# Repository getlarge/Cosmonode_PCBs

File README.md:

# Cosmonode v0.7

Universal node, plug and play extensions to ease sensors connection.

### Features

	- Compile and flash with Arduino IDE
	- MCU = ATMega328P-AU
	- radio = RN2483 / RFM69CW ( communications based on LoRaWan or MySensors protocol )
	- 3.3V regulation ( XC6206P332MR )
	- Powered by 3.7V LiPo battery ( 2 pins JST connector )
	- Battery charging ( MCP7831 )
	- State LED's
	- Jumpers to activate radio reset, LED's, on/off switch
	- Button for reset / config mode, or anything else!
	- ATSHA204 to allow hardware unique signature ( no use with RN2483 )

### Projects

Each directory contains Kicad plans, 3D plans, gerber, descriptive .png and .pdf files.

	- ext01 : BME280, Temperature + Humidity + Pression sensor ( only here for the footprint )
	- ext02 : XKC-Y25, Liquid level sensor
	- ext03 : Various connectors ( I2C, Digital, Analog )
	- ext04 : PT100 3 wire, Temperature sensor
	- ext05 : ISP header + micro USB to TTL 
	- ext06 : Analog pH Sensor - BNC probe (WIP)
	- ext07 : MHZ19, CO2 sensor

### Board pinout

	- A0 = /
	- A1 = /
	A2 = ATSHA204 Input
	A3 = Battery voltage report
	A4 = SDA
	A5 = SCL
	A6 = * LED, jumper J9 ( used as RN2483 Tx )
	A7 = * LED, jumper J14 ( used as RN2483 Rx )
	D0 = RX
	D1 = TX
	D2 = * WakeInterrupt from RN2483, jumper J6 - RFM69 DI0
	D3 = ButtonInterrupt, jumper JP2 ( used to chose mode )
	D4 = /
	D5 = /
	D6 = /
	D7 = /
	D8 = /
	D9 = * RN2483 Reset, jumper J3 - RFM69 Reset
	D10 = RN2483 Rx - RFM69 NSS
	D11 = RN2483 Tx - RFM69 MOSI
	D12 = RFM69 MISO
	D13 = RFM69 SCK
	*optionnal, solder jumper

### Roadmap

--> changelog.md

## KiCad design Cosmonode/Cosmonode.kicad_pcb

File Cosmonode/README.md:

# Cosmonode

The core is based on ATMega328P-AU, RFM69CW, M25P40

Features :

- Compile and flash with arduino
- RF communications based on MySensors protocol
- OTA upload
- Powered by LiPo battery ( 2 pins JST connector )
- ATSHA204 to allow hardware unique signature 
- Universal node, plug and play extensions to ease sensors connection

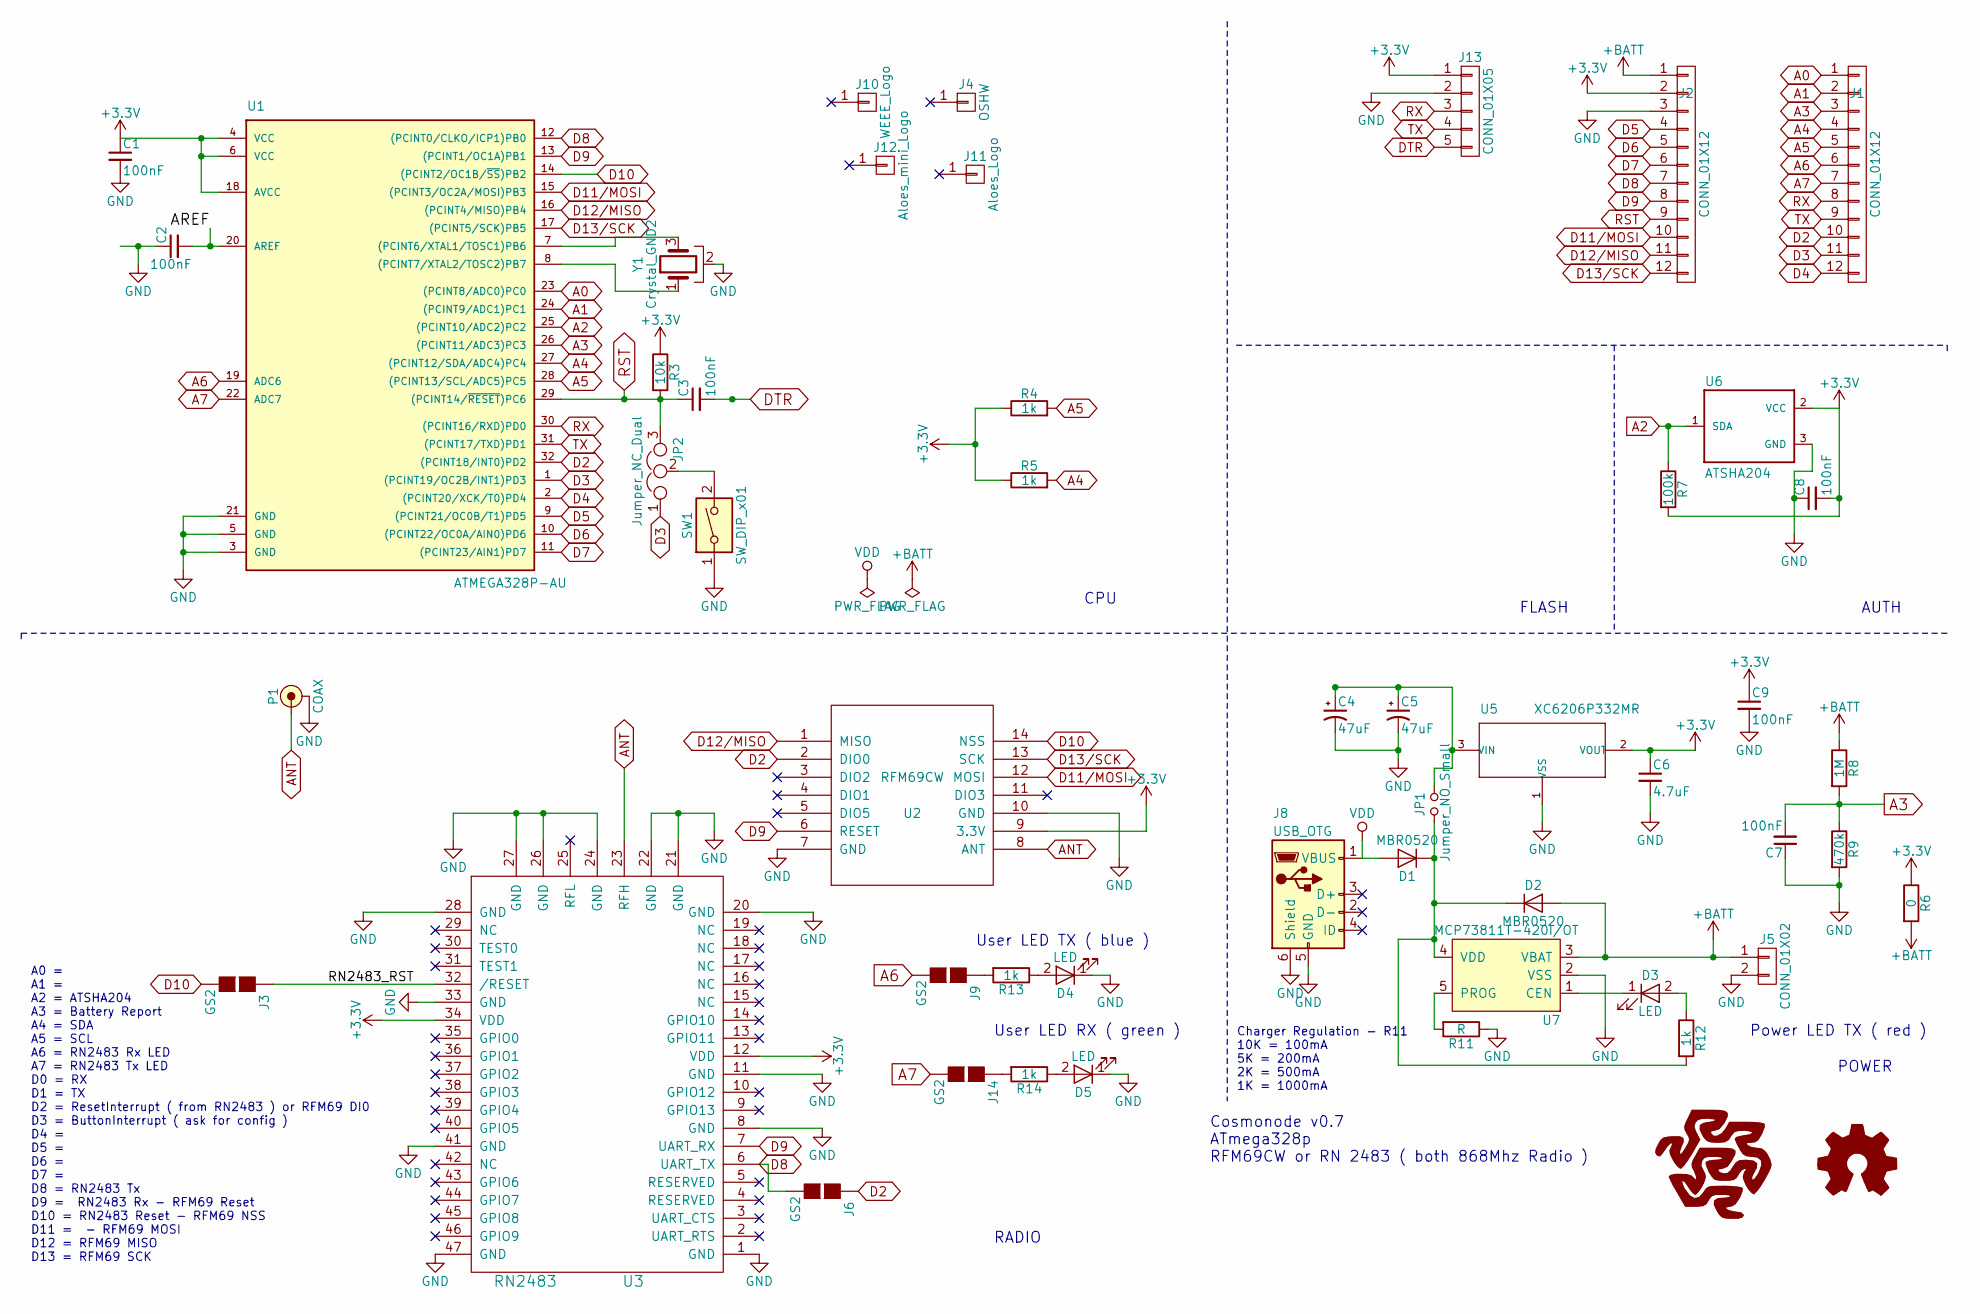
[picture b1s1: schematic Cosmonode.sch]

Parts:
C1, C2, C3, C7, C8, C9: 100nF; C_0603_HandSoldering
C4, C5: 47uF; CP_Tantalum_Case-A_EIA-3216-18_Reflow
C6: 4.7uF; C_0603_HandSoldering
D1, D2: MBR0520; D_SOD-123
D3, D4, D5: LED; LED_0603_HandSoldering
J1, J2: CONN_01X12; Pin_Header_Straight_1x12_Pitch2.54mm
J3, J6, J9, J14: GS2
J4: OSHW; OSHW-Logo_7.5x8mm_Copper
J5: CONN_01X02; JST_PH_B2B-PH-K_02x2.00mm_Straight
J8: USB_OTG; USB_Micro-B_Molex-105017-0001
J10: WEEE_Logo; WEEE-Logo_4.2x6mm_SilkScreen
J11: Aloes_Logo; Aloes
J12: Aloes_mini_Logo; Aloes_mini
J13: CONN_01X05; Pin_Header_Straight_1x05_Pitch2.54mm
JP1: Jumper_NO_Small; Pin_Header_Straight_1x02_Pitch2.54mm
JP2: Jumper_NC_Dual; Pin_Header_Straight_1x03_Pitch2.54mm
P1: COAX; EDGE_SMA_5; Farnell 1608592
R3: 10k; R_0603_HandSoldering
R4, R5, R12, R13, R14: 1k; R_0603_HandSoldering
R6: 0; R_0603_HandSoldering
R7: 100k; R_0603_HandSoldering
R8: 1M; R_0603_HandSoldering
R9: 470k; R_0603_HandSoldering
R11: R; R_0603_HandSoldering
SW1: SW_DIP_x01; SW_Tactile_SPST_Angled_PTS645Vx58-2LFS
U1: ATMEGA328P-AU; TQFP-32_7x7mm_Pitch0.8mm
U2: RFM69CW; RFM12B_SMD
U3: RN2483
U5: XC6206P332MR; TSOT-23
U6: ATSHA204; TSOT-23
U7: MCP73811T-420I/OT; SOT-23-5_HandSoldering
Y1: Crystal_GND2; X3-SMD-3.6X1.3X0.8MM

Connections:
+3V3: C1.1, C6.1, C8.2, C9.1, J2.2, J13.1, R3.1, R4.1, R5.1, R6.1, R7.2, U1.4 (VCC), U1.6 (VCC), U1.18 (AVCC), U2.9 (3.3V), U3.12 (VDD), U3.34 (VDD), U5.2 (VOUT), U6.2 (VCC)
+BATT: D2.2 (A), J2.1, J5.1, R6.2, R8.1, U7.3 (VBAT)
/AREF: C2.2, U1.20 (AREF)
/RN2483_RST: J3.1 (G1), U3.32 (/RESET)
A0: J1.1, U1.23 ((PCINT8/ADC0)PC0)
A1: J1.2, U1.24 ((PCINT9/ADC1)PC1)
A2: R7.1, U1.25 ((PCINT10/ADC2)PC2), U6.1 (SDA)
A3: C7.2, J1.3, R8.2, R9.1, U1.26 ((PCINT11/ADC3)PC3)
A4: J1.4, R5.2, U1.27 ((PCINT12/SDA/ADC4)PC4)
A5: J1.5, R4.2, U1.28 ((PCINT13/SCL/ADC5)PC5)
A6: J1.6, J9.2 (G2), U1.19 (ADC6)
A7: J1.7, J14.2 (G2), U1.22 (ADC7)
ANT: P1.1 (RF), U2.8 (ANT), U3.23 (RFH)
D2: J1.10, J6.1 (G1), U1.32 ((PCINT18/INT0)PD2), U2.2 (DIO0)
D3: J1.11, JP2.1, U1.1 ((PCINT19/OC2B/INT1)PD3)
D4: J1.12, U1.2 ((PCINT20/XCK/T0)PD4)
D5: J2.4, U1.9 ((PCINT21/OC0B/T1)PD5)
D6: J2.5, U1.10 ((PCINT22/OC0A/AIN0)PD6)
D7: J2.6, U1.11 ((PCINT23/AIN1)PD7)
D8: J2.7, J6.2 (G2), U1.12 ((PCINT0/CLKO/ICP1)PB0), U3.6 (UART_TX)
D9: J2.8, U1.13 ((PCINT1/OC1A)PB1), U2.6 (RESET), U3.7 (UART_RX)
D10: J3.2 (G2), U1.14 ((PCINT2/OC1B/~SS~)PB2), U2.14 (NSS)
D11/MOSI: J2.10, U1.15 ((PCINT3/OC2A/MOSI)PB3), U2.12 (MOSI)
D12/MISO: J2.11, U1.16 ((PCINT4/MISO)PB4), U2.1 (MISO)
D13/SCK: J2.12, U1.17 ((PCINT5/SCK)PB5), U2.13 (SCK)
DTR: C3.2, J13.5
GND: C1.2, C2.1, C4.2, C5.2, C6.2, C7.1, C8.1, C9.2, D4.1 (K), D5.1 (K), J2.3, J5.2, J8.5 (GND), J8.6 (Shield), J13.2, P1.2 (GND), R9.2, R11.1, SW1.1, U1.3 (GND), U1.5 (GND), U1.21 (GND), U2.7 (GND), U2.10 (GND), U3.1 (GND), U3.8 (GND), U3.11 (GND), U3.20 (GND), U3.21 (GND), U3.22 (GND), U3.24 (GND), U3.26 (GND), U3.27 (GND), U3.28 (GND), U3.33 (GND), U3.41 (GND), U3.47 (GND), U5.1 (VSS), U6.3 (GND), U7.2 (VSS), Y1.2
unnamed: C4.1, C5.1, JP1.2, U5.3 (VIN)
unnamed: D1.1 (K), D2.1 (K), JP1.1, R12.2, U7.4 (VDD)
unnamed: D3.1 (K), U7.1 (CEN)
unnamed: D3.2 (A), R12.1
unnamed: D4.2 (A), R13.1
unnamed: D5.2 (A), R14.1
unnamed: J9.1 (G1), R13.2
unnamed: J14.1 (G1), R14.2
unnamed: JP2.2, SW1.2
unnamed: R11.2, U7.5 (PROG)
unnamed: U1.7 ((PCINT6/XTAL1/TOSC1)PB6), Y1.3
unnamed: U1.8 ((PCINT7/XTAL2/TOSC2)PB7), Y1.1
RST: C3.1, J2.9, JP2.3, R3.2, U1.29 ((PCINT14/~RESET~)PC6)
RX: J1.8, J13.3, U1.30 ((PCINT16/RXD)PD0)
TX: J1.9, J13.4, U1.31 ((PCINT17/TXD)PD1)
VDD: D1.2 (A), J8.1 (VBUS)

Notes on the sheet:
CPU
FLASH
AUTH
POWER
RADIO
Cosmonode v0.7 ATmega328p RFM69CW or RN 2483 ( both 868Mhz Radio )
Charger Regulation - R11 10K = 100mA 5K = 200mA 2K = 500mA 1K = 1000mA
User LED TX ( blue )
User LED RX ( green )
Power LED TX ( red )
A0 = A1 = A2 = ATSHA204 A3 = Battery Report A4 = SDA A5 = SCL A6 = RN2483 Rx LED A7 = RN2483 Tx LED D0 = RX D1 = TX D2 = ResetInterrupt ( from RN2483 ) or RFM69 DI0 D3 = ButtonInterrupt ( ask for config ) D4 = D5 = D6 = D7 = D8 = RN2483 Tx D9 = RN2483 Rx - RFM69 Reset D10 = RN2483 Reset - RFM69 NSS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

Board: 2 copper layers, 49 parts (6 on the bottom side), 43 nets, no tracks yet.

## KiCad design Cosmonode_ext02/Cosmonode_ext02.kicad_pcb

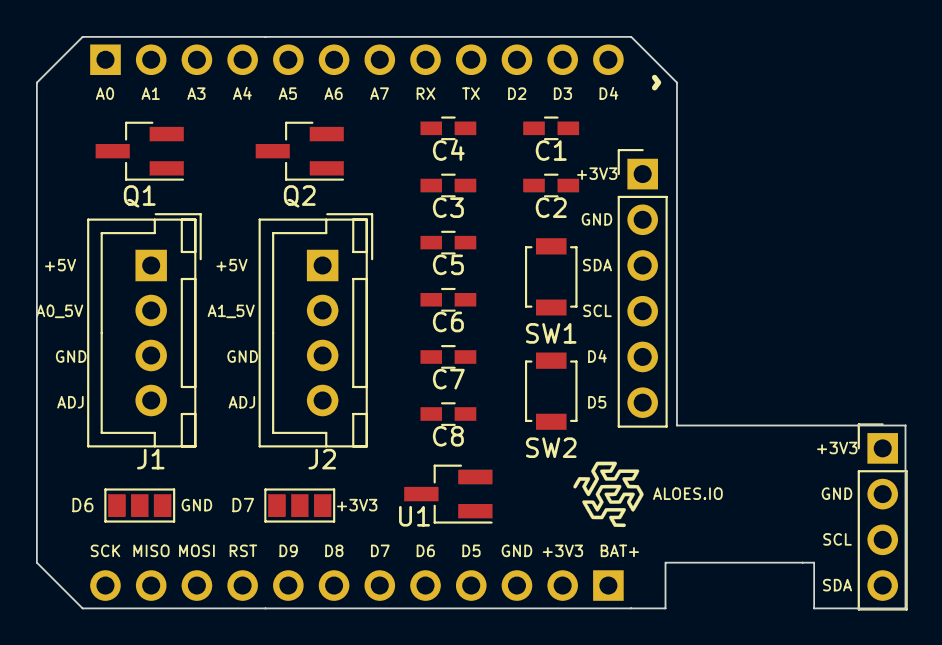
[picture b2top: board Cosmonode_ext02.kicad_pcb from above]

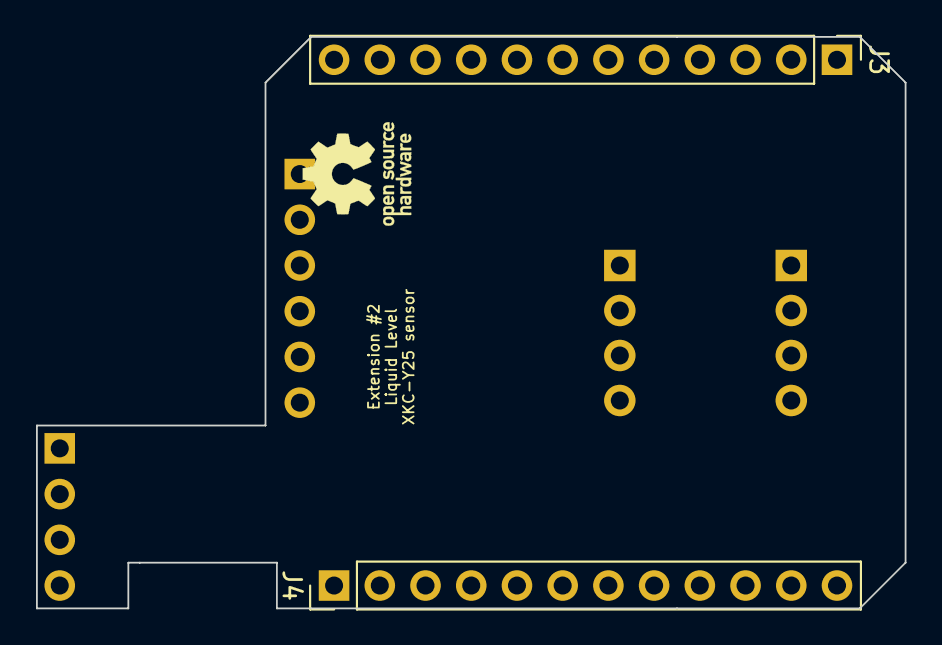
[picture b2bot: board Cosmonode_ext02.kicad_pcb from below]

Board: 2 copper layers, 48.3 x 31.8 mm, 23 parts (3 on the bottom side), 17 nets, no tracks yet.

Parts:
C1, C3, C4, C5, C7, C8: 100nF; C_0603_HandSoldering
C2, C6: 10uF; C_0603_HandSoldering
J1, J2: CONN_01X04; JST_XH_B04B-XH-A_04x2.50mm_Straight
J3, J4: CONN_01X12; Socket_Strip_Straight_1x12_Pitch2.54mm
J5, J6: GS3
J7: Aloes_Logo; Aloes_mini
J8: OSHW_Logo; OSHW-Logo_5.7x6mm_SilkScreen
J9: CONN_01X04; Socket_Strip_Straight_1x04_Pitch2.54mm
J10: CONN_01X06; Pin_Header_Straight_1x06_Pitch2.54mm
Q1, Q2: BSS138; SOT-23_Handsoldering
SW1, SW2: SW_Push; SW_SPST_B3U-1000P
U1: XC6206P502MR; SOT-23_Handsoldering

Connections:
+3V3: J4.2, J5.3, J9.1, J10.1, Q1.1, Q2.1
+5V: C2.1, C3.1, C6.1, C7.1, J1.1, J2.1, U1.2
A0: J3.1, Q1.2
A0_5V: C4.1, J1.2, Q1.3
A1: J3.2, Q2.2
A1_5V: C8.1, J2.2, Q2.3
A4: J3.4, J9.4, J10.3
A5: J3.5, J9.3, J10.4
D4: J3.12, J10.5
D5: J4.4, J10.6
D6: J4.5, J6.1
D7: J4.6, J5.1
GND: J4.3, J6.3, J9.2, J10.2
unnamed: C1.1, C2.2, C3.2, C4.2, C5.1, C6.2, C7.2, C8.2, J1.3, J2.3, J6.2, SW1.2, SW2.2, U1.1
unnamed: C1.2, J1.4, SW1.1
unnamed: C5.2, J2.4, SW2.1
unnamed: J5.2, U1.3

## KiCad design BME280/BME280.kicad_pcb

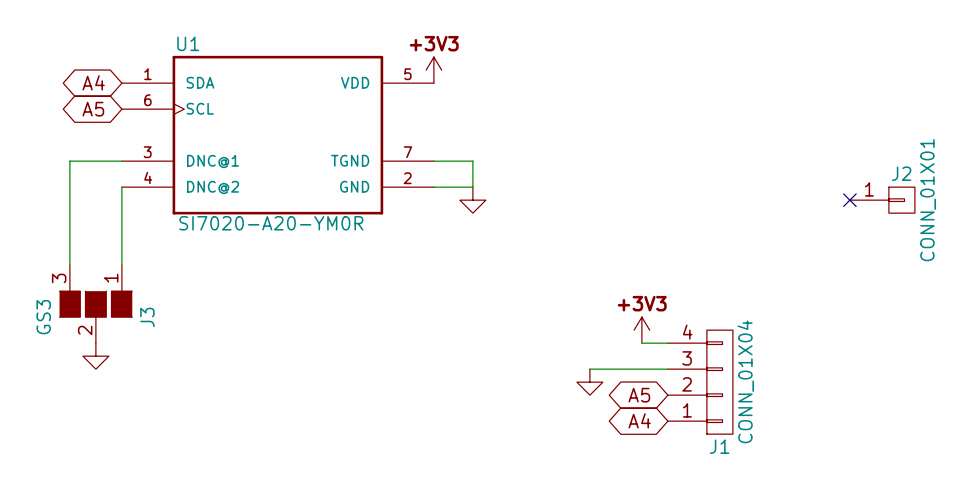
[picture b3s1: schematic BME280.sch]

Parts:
J1: CONN_01X04; Pin_Header_Angled_1x04_Pitch2.54mm
J2: CONN_01X01; MountingHole_2.5mm
J3: GS3
U1: SI7020-A20-YM0R; SON100P300X300X80-7N

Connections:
+3V3: J1.4, U1.5 (VDD)
A4: J1.1, U1.1 (SDA)
A5: J1.2, U1.6 (SCL)
GND: J1.3, J3.2 (G2), U1.2 (GND), U1.7 (TGND)
unnamed: J3.1 (G1), U1.4 (DNC@2)
unnamed: J3.3 (G3), U1.3 (DNC@1)

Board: 2 copper layers, 4 parts (1 on the bottom side), 6 nets, no tracks yet.

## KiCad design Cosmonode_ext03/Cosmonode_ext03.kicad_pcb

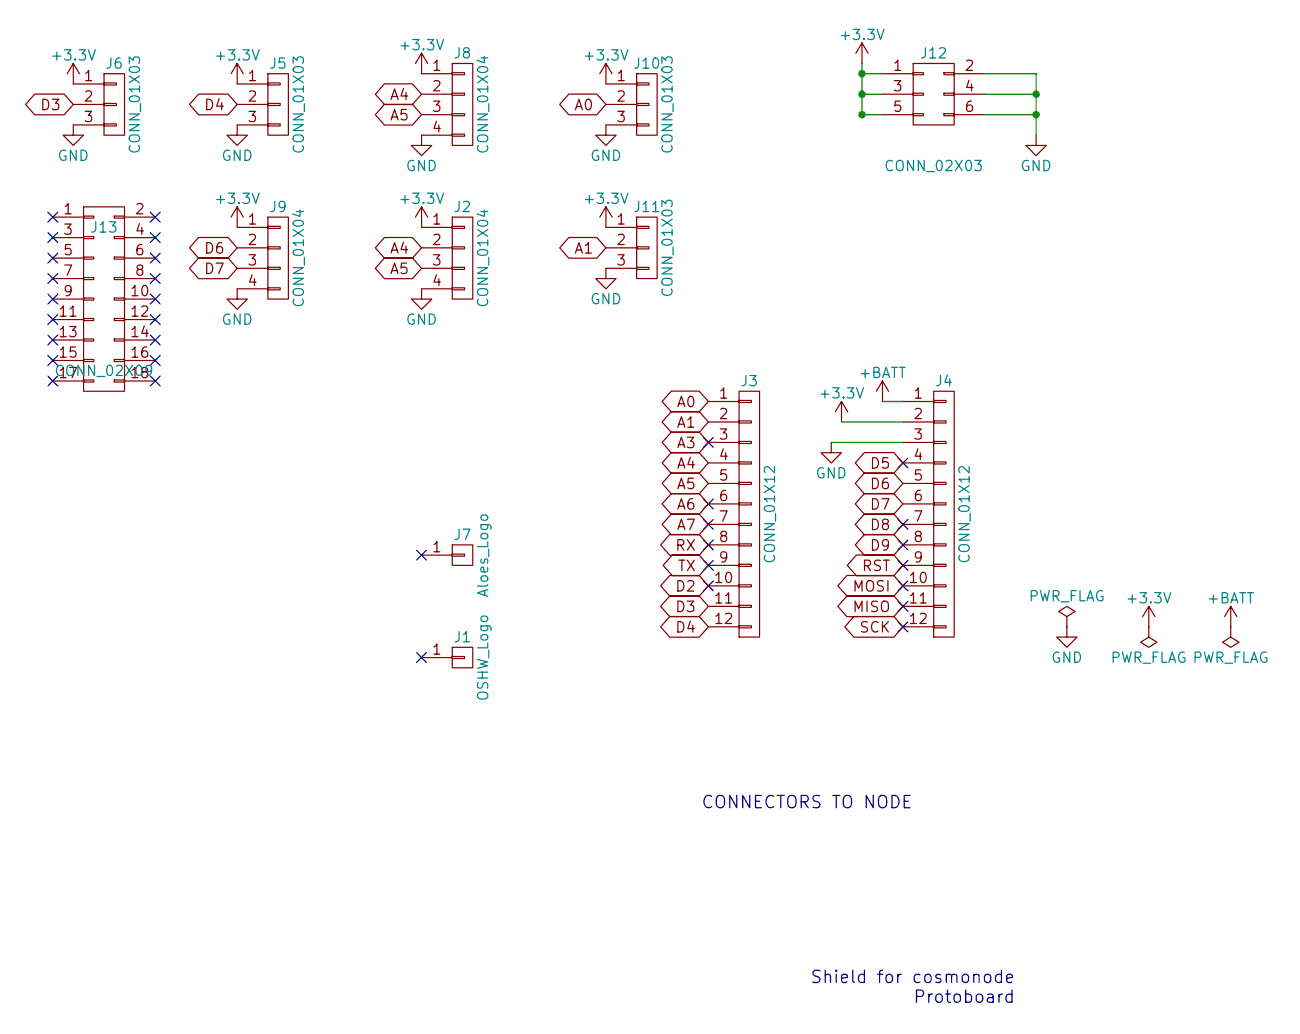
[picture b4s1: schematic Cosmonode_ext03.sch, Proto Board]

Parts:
J1: OSHW_Logo; OSHW-Logo_5.7x6mm_SilkScreen
J2, J8, J9: CONN_01X04; Pin_Header_Straight_1x04_Pitch2.54mm
J3, J4: CONN_01X12; Socket_Strip_Straight_1x12_Pitch2.54mm
J5, J6, J10, J11: CONN_01X03; Pin_Header_Straight_1x03_Pitch2.54mm
J7: Aloes_Logo; Aloes_mini
J12: CONN_02X03; Pin_Header_Straight_2x03_Pitch2.54mm
J13: CONN_02X09; Pin_Header_Straight_2x09_Pitch2.54mm

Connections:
+3V3: J2.1, J4.2, J5.1, J6.1, J8.1, J9.1, J10.1, J11.1, J12.1, J12.3, J12.5
+BATT: J4.1
A0: J3.1, J10.2
A1: J3.2, J11.2
A3: J3.3
A4: J2.2, J3.4, J8.2
A5: J2.3, J3.5, J8.3
A6: J3.6
A7: J3.7
D2: J3.10
D3: J3.11, J6.2
D4: J3.12, J5.2
D5: J4.4
D6: J4.5, J9.2
D7: J4.6, J9.3
D8: J4.7
D9: J4.8
GND: J2.4, J4.3, J5.3, J6.3, J8.4, J9.4, J10.3, J11.3, J12.2, J12.4, J12.6
MISO: J4.11
MOSI: J4.10
RST: J4.9
RX: J3.8
SCK: J4.12
TX: J3.9

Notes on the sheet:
Shield for cosmonode Protoboard
CONNECTORS TO NODE

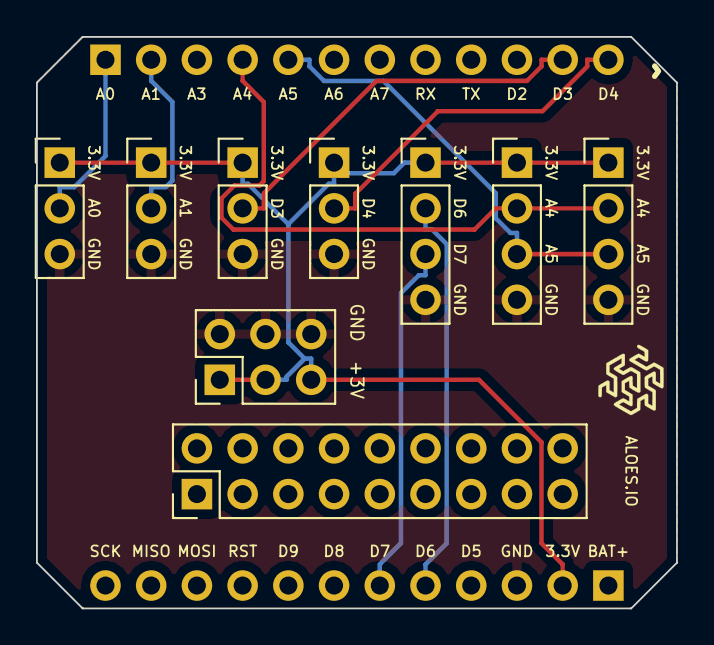
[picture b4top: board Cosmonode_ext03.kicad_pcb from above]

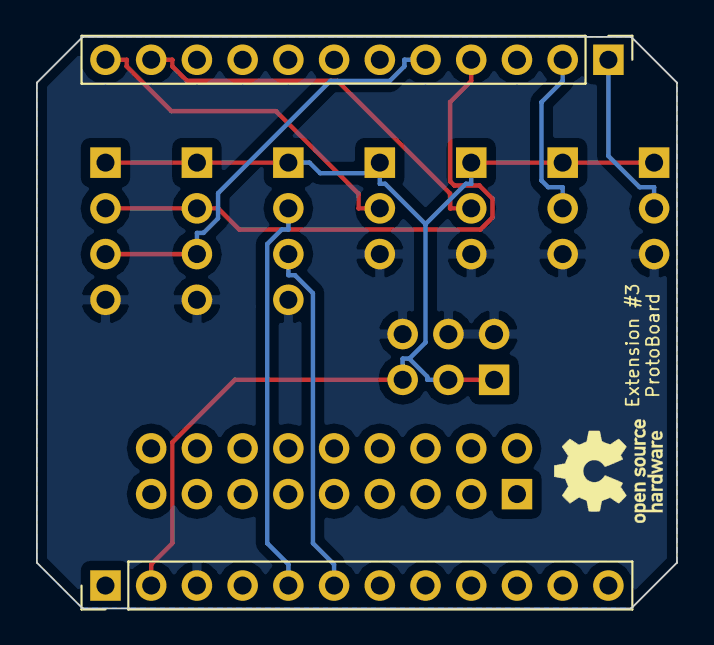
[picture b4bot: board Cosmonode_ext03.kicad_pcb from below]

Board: 2 copper layers, 35.6 x 31.8 mm, 13 parts (3 on the bottom side), 10 nets.

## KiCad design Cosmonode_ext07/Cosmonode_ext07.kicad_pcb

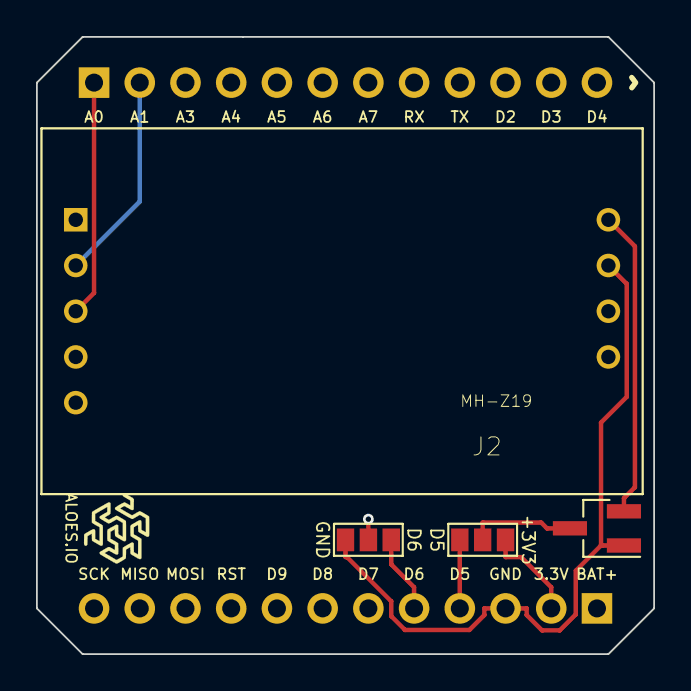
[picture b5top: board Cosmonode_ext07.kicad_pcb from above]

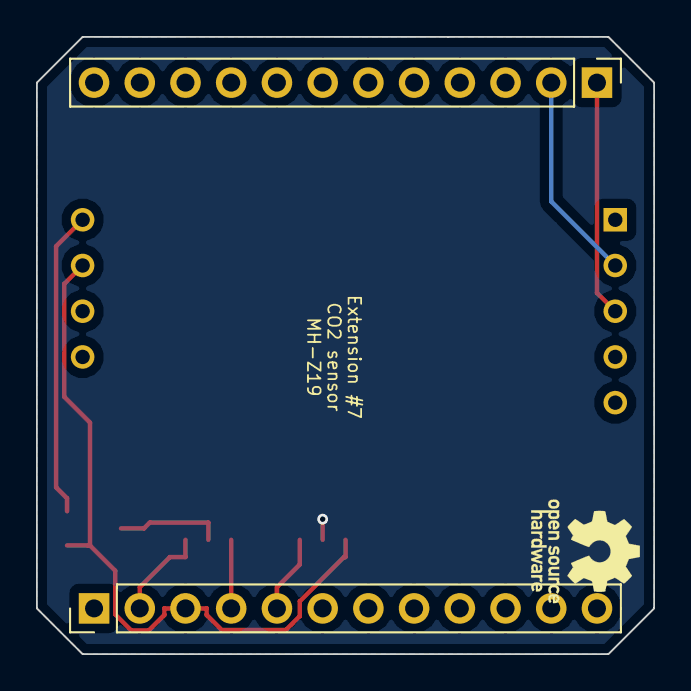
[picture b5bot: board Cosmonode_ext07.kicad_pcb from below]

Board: 2 copper layers, 34.3 x 34.3 mm, 8 parts (3 on the bottom side), 8 nets.

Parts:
J1: OSHW_Logo; OSHW-Logo_5.7x6mm_SilkScreen
J2: MH-Z19
J3, J4: CONN_01X12; Pin_Header_Straight_1x12_Pitch2.54mm
J5, J6: GS3
J7: Aloes_Logo; Aloes_mini
U1: XC6206P502MR; SOT-23_Handsoldering

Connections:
+3V3: J4.2, J5.3
+5V: J2.6, U1.2
A0: J2.3, J3.1
A1: J2.2, J3.2
D5: J4.4, J5.1
D6: J4.5, J6.1
GND: J2.7, J4.3, J6.3, U1.1
unnamed: J5.2, U1.3

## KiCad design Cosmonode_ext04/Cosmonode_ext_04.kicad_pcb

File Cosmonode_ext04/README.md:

# Cosmonode_ext_04

Extension 4 : includes driver and connector for PT100 sensor (3wire)

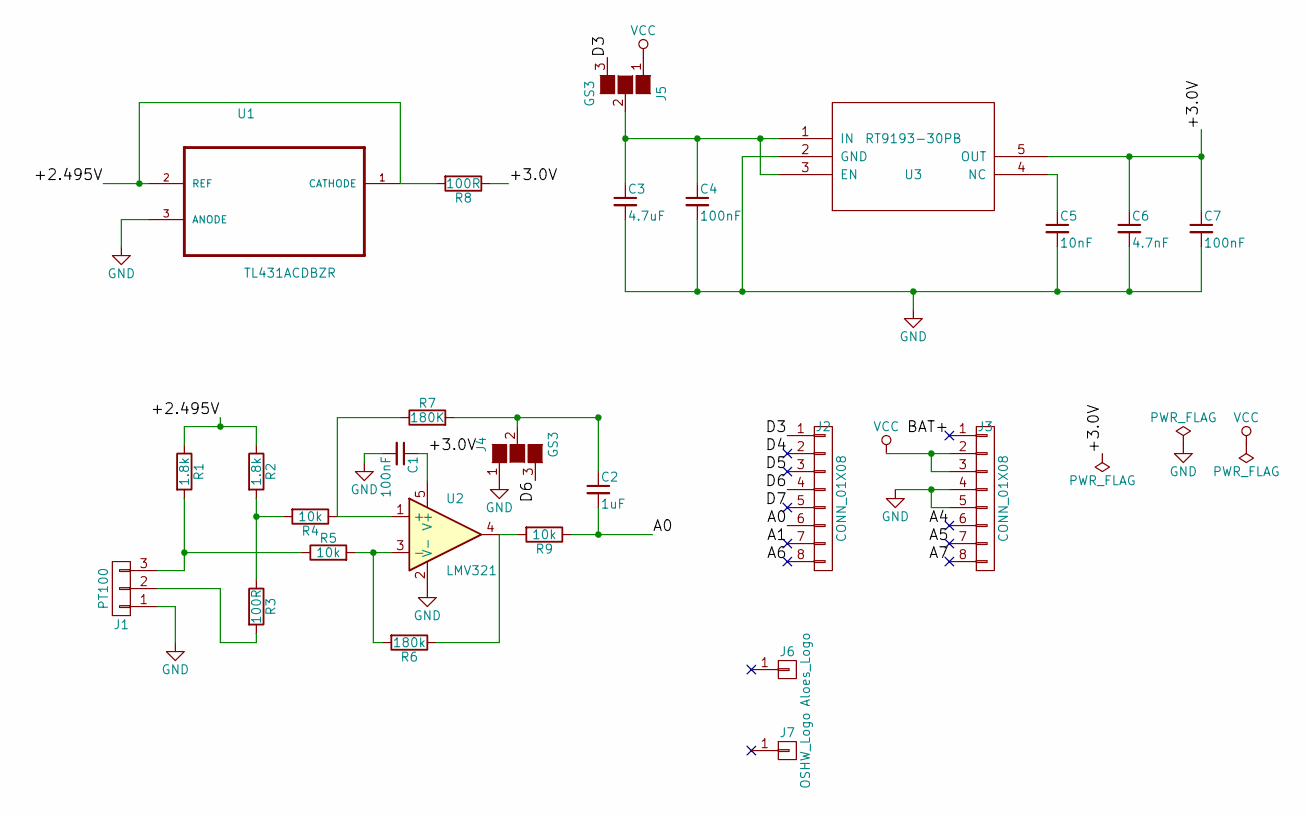
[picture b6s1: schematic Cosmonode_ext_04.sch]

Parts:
C1, C4, C7: 100nF; C_0603_HandSoldering
C2: 1uF; C_0603_HandSoldering
C3: 4.7uF; C_0603_HandSoldering
C5: 10nF; C_0603_HandSoldering
C6: 4.7nF; C_0603_HandSoldering
J1: PT100; JST_XH_B03B-XH-A_03x2.50mm_Straight
J2, J3: CONN_01X08; Socket_Strip_Straight_1x08_Pitch2.54mm
J4, J5: GS3
J6: Aloes_Logo; Aloes_mini
J7: OSHW_Logo; OSHW-Logo_5.7x6mm_SilkScreen
R1, R2: 1.8k; R_0603_HandSoldering
R3, R8: 100R; R_0603_HandSoldering
R4, R5, R9: 10k; R_0603_HandSoldering
R6: 180k; R_0603_HandSoldering
R7: 180K; R_0603_HandSoldering
U1: TL431ACDBZR; SOT-23_Handsoldering
U2: LMV321; SOT-23-5_HandSoldering
U3: RT9193-30PB; SOT-23-5_HandSoldering

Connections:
/+2.495V: R1.1, R2.1, R8.2, U1.1 (CATHODE), U1.2 (REF)
/+3.0V: C1.1, C6.1, C7.1, R8.1, U2.5 (V+), U3.5 (OUT)
/A0: C2.2, J2.6, R9.1
/A1: J2.7
/A4: J3.6
/A5: J3.7
/A6: J2.8
/A7: J3.8
/BAT+: J3.1
/D3: J2.1, J5.3 (G3)
/D4: J2.2
/D5: J2.3
/D6: J2.4, J4.3 (G3)
/D7: J2.5
GND: C1.2, C3.2, C4.2, C5.2, C6.2, C7.2, J1.1, J3.4, J3.5, J4.1 (G1), U1.3 (ANODE), U2.2 (V-), U3.2 (GND)
unnamed: C2.1, J4.2 (G2), R7.2
unnamed: C3.1, C4.1, J5.2 (G2), U3.1 (IN), U3.3 (EN)
unnamed: C5.1, U3.4 (NC)
unnamed: J1.2, R3.2
unnamed: J1.3, R1.2, R5.1
unnamed: R2.2, R3.1, R4.2
unnamed: R4.1, R7.1, U2.1 (+)
unnamed: R5.2, R6.2, U2.3 (-)
unnamed: R6.1, R9.2, U2.4
VCC: J3.2, J3.3, J5.1 (G1)

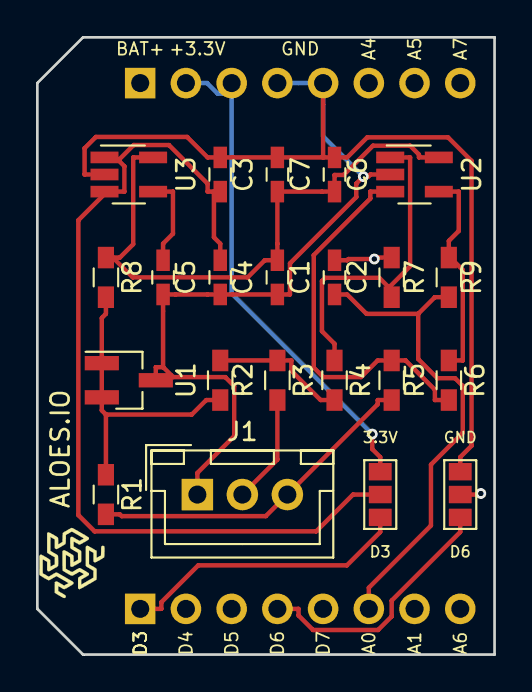
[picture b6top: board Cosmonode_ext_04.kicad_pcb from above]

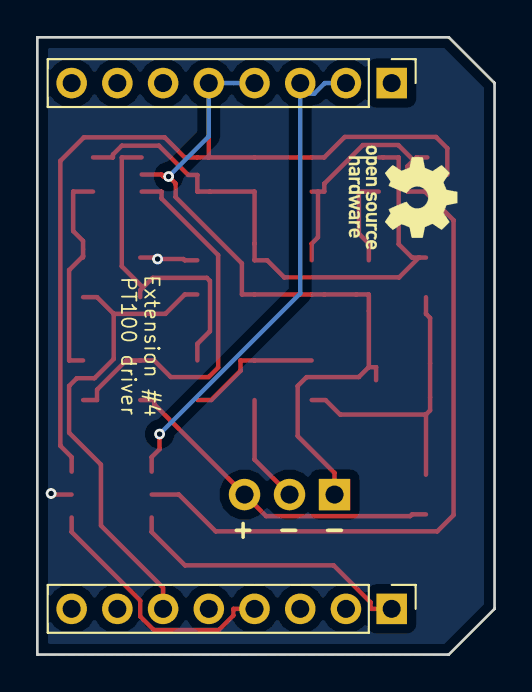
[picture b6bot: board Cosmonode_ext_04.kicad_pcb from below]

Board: 2 copper layers, 25.4 x 34.3 mm, 26 parts (3 on the bottom side), 16 nets.

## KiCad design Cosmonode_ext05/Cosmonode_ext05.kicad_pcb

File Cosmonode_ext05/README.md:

# Cosmonode_ext_05

Extension 5  : - ISP header for bootloader transfer and 
	       - micro USB for serial programming

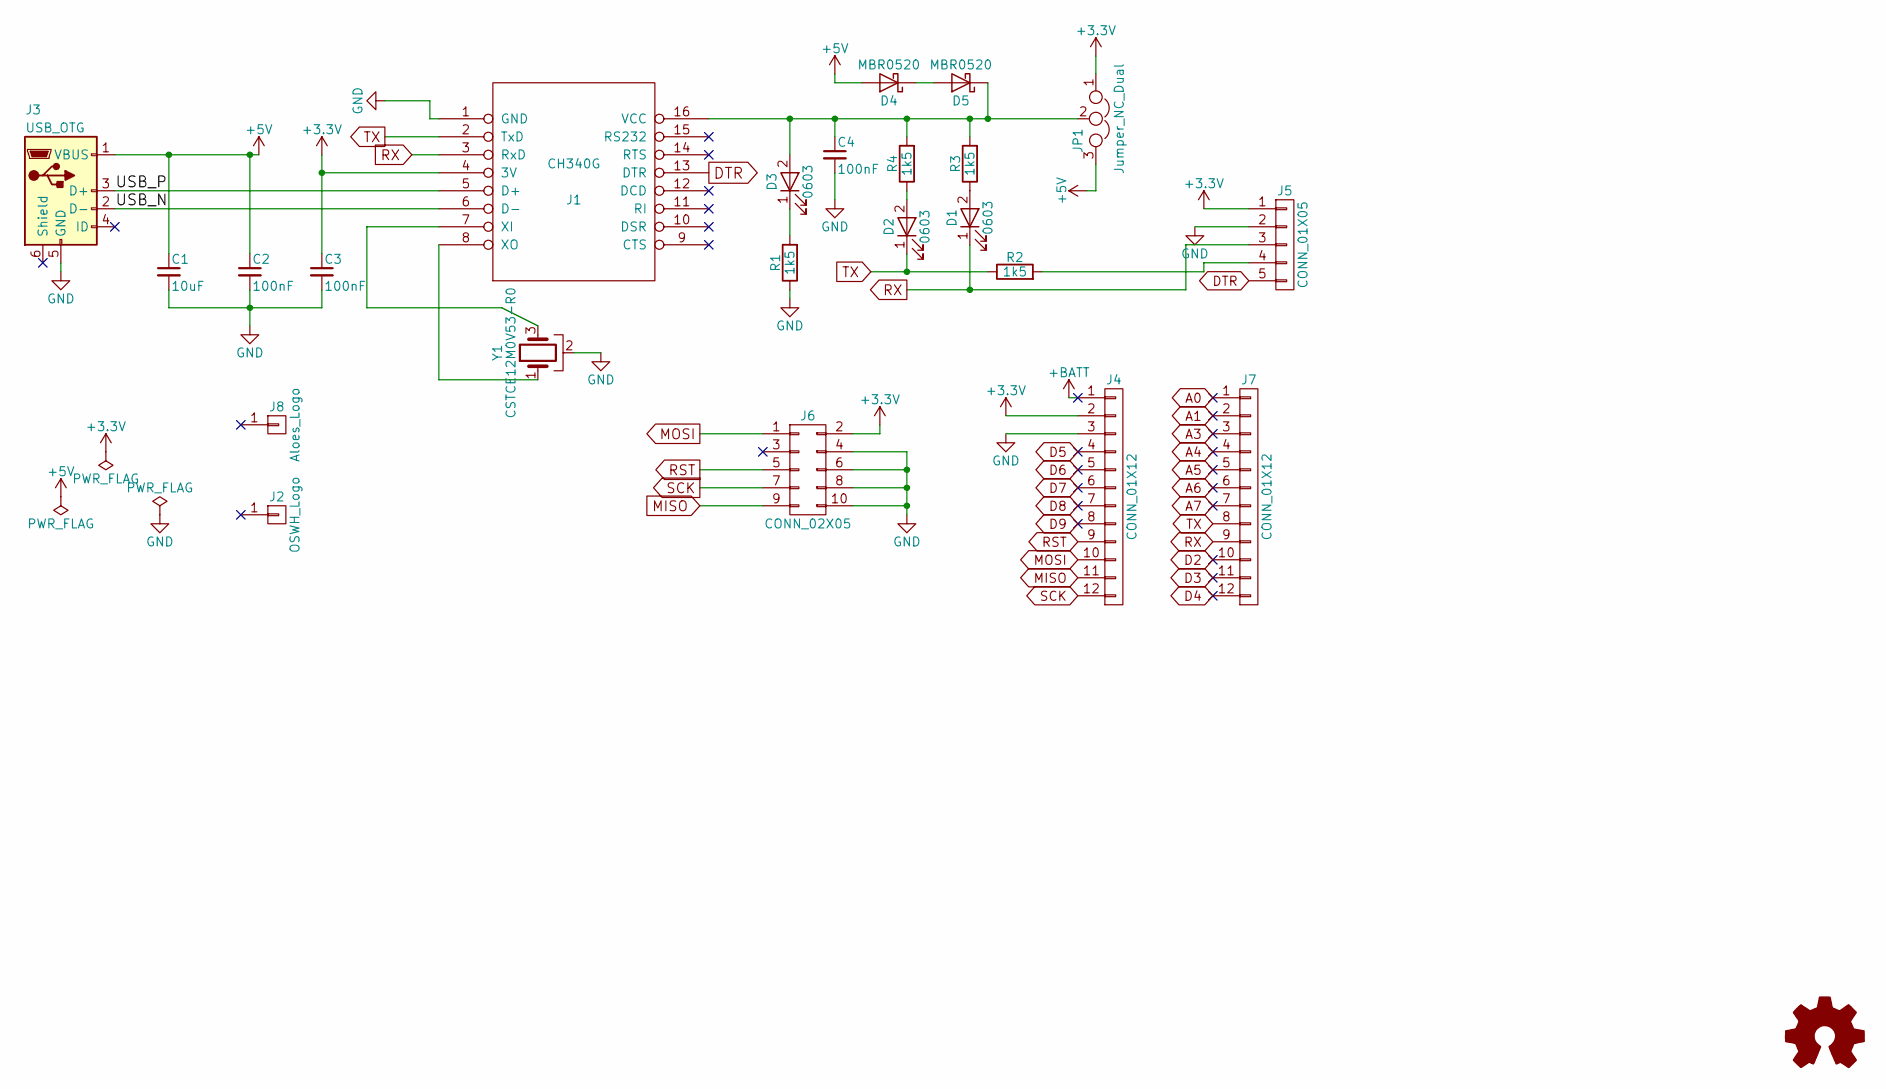
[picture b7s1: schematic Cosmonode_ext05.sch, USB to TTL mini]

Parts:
C1: 10uF; C_0603_HandSoldering
C2, C3, C4: 100nF; C_0603_HandSoldering
D1, D2, D3: 0603; LED_0603
D4, D5: MBR0520; D_SOD-123
J1: CH340G; SOIC-16_3.9x9.9mm_Pitch1.27mm
J2: OSWH_Logo; OSHW-Logo_5.7x6mm_SilkScreen
J3: USB_OTG; USB_Micro-B_Molex-105017-0001
J4, J7: CONN_01X12; Socket_Strip_Straight_1x12_Pitch2.54mm
J5: CONN_01X05; Socket_Strip_Straight_1x05_Pitch2.54mm
J6: CONN_02X05; Pin_Header_Straight_2x05_Pitch2.54mm
J8: Aloes_Logo; Aloes_mini
JP1: Jumper_NC_Dual; Pin_Header_Straight_1x03_Pitch2.54mm
R1, R2, R3, R4: 1k5; R_0603_HandSoldering
Y1: CSTCE12M0V53-R0; X3-SMD-3.6X1.3X0.8MM

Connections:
+3V3: C3.1, J1.4 (3V), J4.2, J5.1, J6.2, JP1.1; also elsewhere on the board
+5V: C1.1, C2.1, D4.2 (A), J3.1 (VBUS), JP1.3
+BATT: J4.1
/USB_N: J1.6 (D-), J3.2 (D-); also elsewhere on the board
/USB_P: J1.5 (D+), J3.3 (D+); also elsewhere on the board
A0: J7.1
A1: J7.2
A3: J7.3
A4: J7.4
A5: J7.5
A6: J7.6
A7: J7.7
D2: J7.10
D3: J7.11
D4: J7.12
D5: J4.4
D6: J4.5
D7: J4.6
D8: J4.7
D9: J4.8
DTR: J1.13 (DTR), J5.5; also elsewhere on the board
GND: C1.2, C2.2, C3.2, C4.2, J1.1 (GND), J3.5 (GND), J4.3, J5.2, J6.4, J6.6, J6.8, J6.10, R1.1, Y1.2; also elsewhere on the board
MISO: J4.11, J6.9
MOSI: J4.10, J6.1
unnamed 24: C4.1, D3.2 (A), D5.1 (K), J1.16 (VCC), JP1.2, R3.2, R4.2; also elsewhere on the board
unnamed: D1.2 (A), R3.1
unnamed: D2.2 (A), R4.1
unnamed: D3.1 (K), R1.2
unnamed: D4.1 (K), D5.2 (A)
unnamed 29: J1.7 (XI), Y1.3; also elsewhere on the board
unnamed 30: J1.8 (XO), Y1.1; also elsewhere on the board
unnamed: J5.4, R2.2
RST: J4.9, J6.5
RX: D1.1 (K), J1.3 (RxD), J5.3, J7.9; also elsewhere on the board
SCK: J4.12, J6.7
TX: D2.1 (K), J1.2 (TxD), J7.8, R2.1; also elsewhere on the board

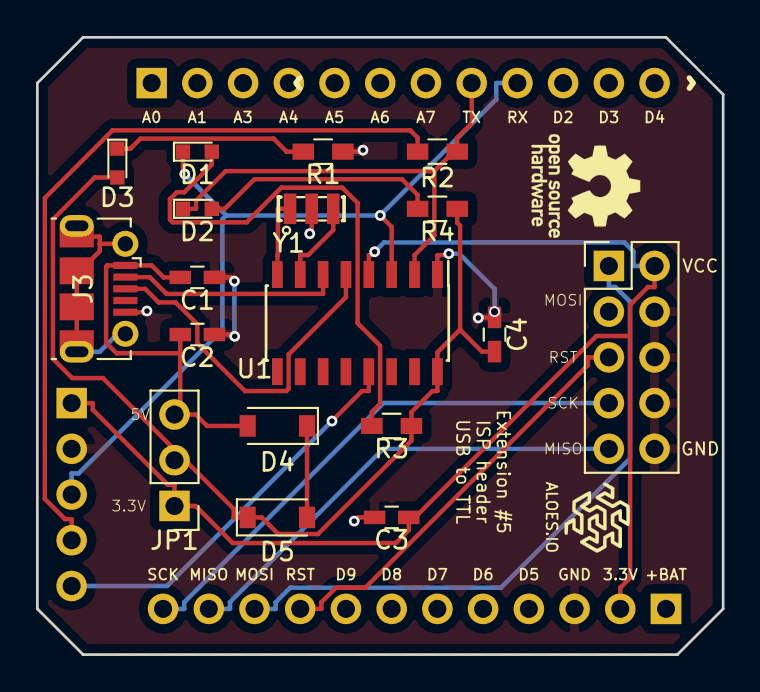
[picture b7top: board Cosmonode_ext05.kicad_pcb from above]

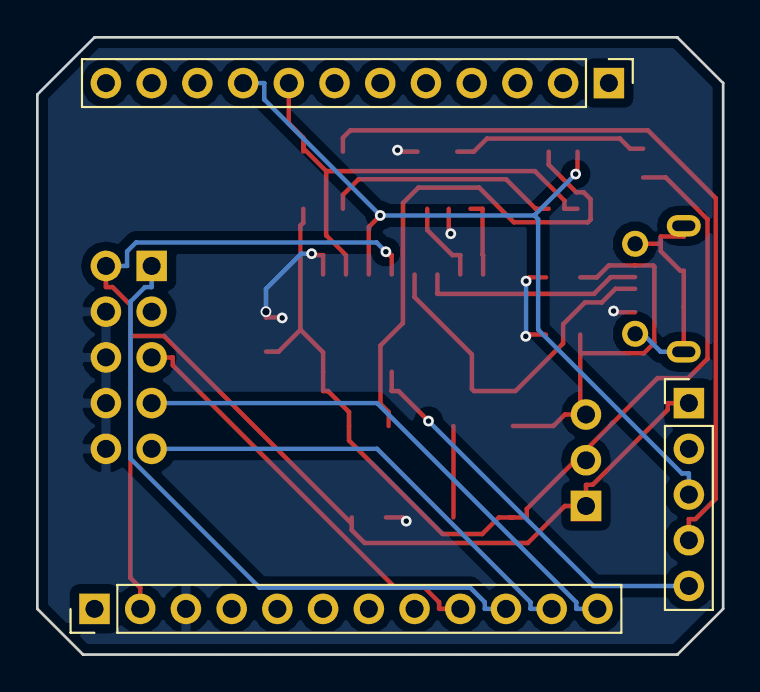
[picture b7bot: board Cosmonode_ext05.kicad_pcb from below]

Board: 2 copper layers, 38.1 x 34.3 mm, 23 parts (3 on the bottom side), 20 nets.

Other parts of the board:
U1: CH340G; SOIC-16_3.9x9.9mm_Pitch1.27mm

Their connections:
+3V3: U1.4; also elsewhere on the board
/USB_N: U1.6; also elsewhere on the board
/USB_P: U1.5; also elsewhere on the board
DTR: U1.13; also elsewhere on the board
GND: U1.1; also elsewhere on the board
unnamed 24: U1.16; also elsewhere on the board
unnamed 29: U1.7; also elsewhere on the board
unnamed 30: U1.8; also elsewhere on the board
RX: U1.3; also elsewhere on the board
TX: U1.2; also elsewhere on the board
